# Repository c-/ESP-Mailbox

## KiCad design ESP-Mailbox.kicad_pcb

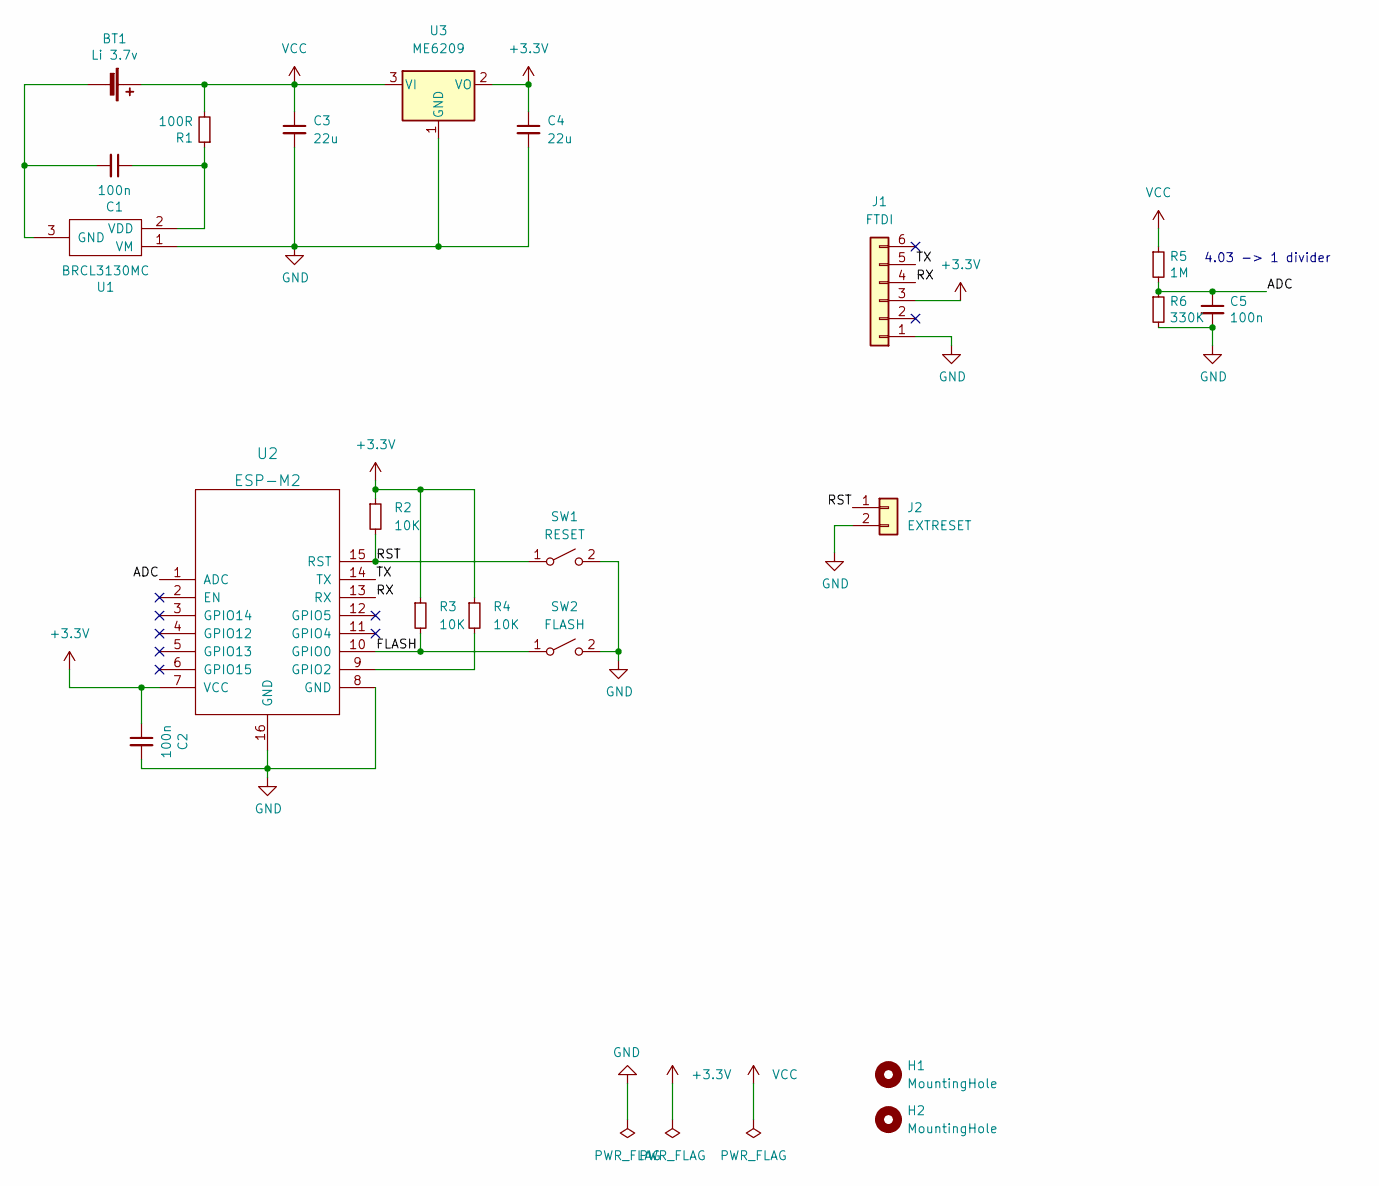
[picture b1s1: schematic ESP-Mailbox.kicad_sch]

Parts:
BT1: Li 3.7v; Battery_18650_Unprotected_Clip
C1, C2, C5: 100n; C_0603_1608Metric_Pad1.08x0.95mm_HandSolder
C3, C4: 22u; C_0805_2012Metric_Pad1.18x1.45mm_HandSolder
H1, H2: MountingHole; MountingHole_3.2mm_M3
J1: FTDI; Socket_Strip_Straight_1x06_Oval_Pitch2.54mm
J2: EXTRESET; JST_XH_B2B-XH-A_1x02_P2.50mm_Vertical
R1: 100R; R_0603_1608Metric_Pad0.98x0.95mm_HandSolder
R2, R3, R4: 10K; R_0603_1608Metric_Pad0.98x0.95mm_HandSolder
R5: 1M; R_0603_1608Metric_Pad0.98x0.95mm_HandSolder
R6: 330K; R_0603_1608Metric_Pad0.98x0.95mm_HandSolder
SW1: RESET; SW_PUSH_4.5mm
SW2: FLASH; SW_PUSH_4.5mm
U1: BRCL3130MC; SOT-23_Handsoldering
U2: ESP-M2
U3: ME6209; SOT-23_Handsoldering

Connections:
+3.3V: C2.1, C4.1, J1.3, R2.1, R3.1, R4.1, U2.7 (VCC), U3.2 (VO)
/ADC: C5.1, R5.2, R6.1, U2.1 (ADC)
/FLASH: R3.2, SW2.1 (A), U2.10 (GPIO0)
/RST: J2.1, R2.2, SW1.1 (A), U2.15 (RST)
/RX: J1.4, U2.13 (RX)
/TX: J1.5, U2.14 (TX)
GND: C2.2, C3.2, C4.2, C5.2, J1.1, J2.2, R6.2, SW1.2 (B), SW2.2 (B), U1.1 (VM), U2.8 (GND), U2.16 (GND), U3.1 (GND)
unnamed: BT1.2 (-), C1.2, U1.3 (GND)
unnamed: C1.1, R1.1, U1.2 (VDD)
unnamed: R4.2, U2.9 (GPIO2)
VCC: BT1.1 (+), C3.1, R1.2, R5.1, U3.3 (VI)

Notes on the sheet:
4.03 -> 1 divider

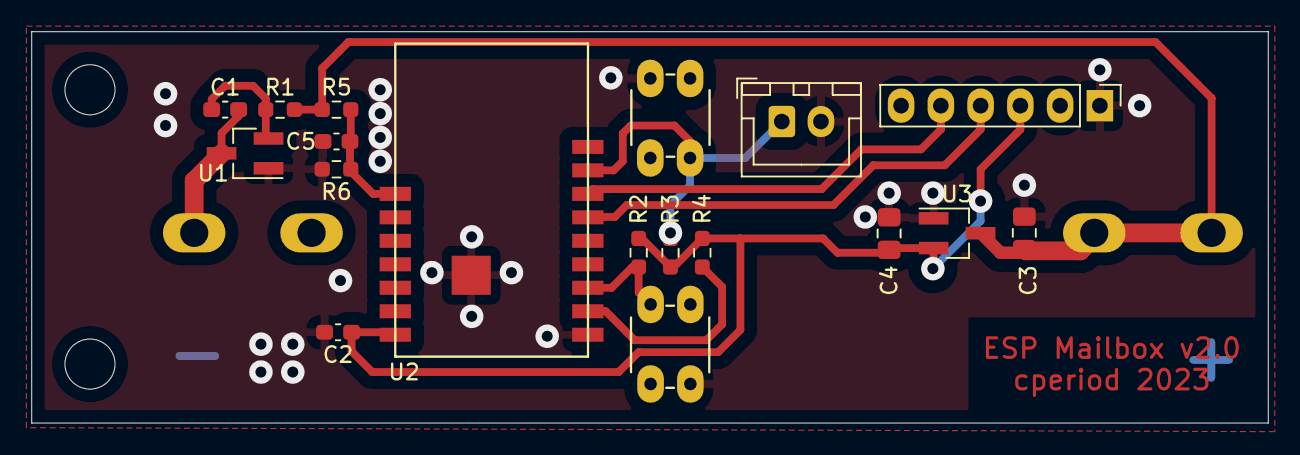
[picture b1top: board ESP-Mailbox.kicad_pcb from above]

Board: 2 copper layers, 79.0 x 25.0 mm, 21 parts (1 on the bottom side), 11 nets.

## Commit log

2023-03-12 initial import
